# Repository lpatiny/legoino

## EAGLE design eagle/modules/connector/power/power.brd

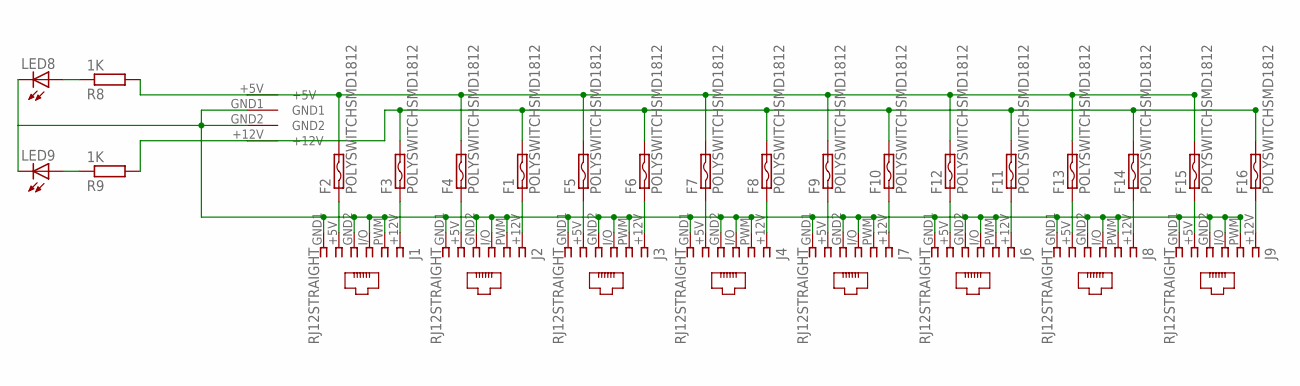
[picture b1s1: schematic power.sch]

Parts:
F1, F2, F3, F4, F5, F6, F7, F8, F9, F10, F11, F12, F13, F14, F15, F16: POLYSWITCHSMD1812; C1812
J1, J2, J3, J4, J6, J7, J8, J9: RJ12STRAIGHT; RJ12-STRAIGHT
LED8, LED9: LED3MM
R8, R9: 1K; M1206
U$1: KPJX-4S-S

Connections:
GND: J1.GND1 (6), J1.GND2 (4), J1.I/O (3), J1.PWM (2), J2.GND1 (6), J2.GND2 (4), J2.I/O (3), J2.PWM (2), J3.GND1 (6), J3.GND2 (4), J3.I/O (3), J3.PWM (2), J4.GND1 (6), J4.GND2 (4), J4.I/O (3), J4.PWM (2), J6.GND1 (6), J6.GND2 (4), J6.I/O (3), J6.PWM (2), J7.GND1 (6), J7.GND2 (4), J7.I/O (3), J7.PWM (2), J8.GND1 (6), J8.GND2 (4), J8.I/O (3), J8.PWM (2), J9.GND1 (6), J9.GND2 (4), J9.I/O (3), J9.PWM (2), LED8.K (C), LED9.K (C), U$1.GND1, U$1.GND2
unnamed: F2.1, J1.+5V (5)
unnamed: F3.1, J1.+12V (1)
unnamed: F4.1, J2.+5V (5)
unnamed: F1.1, J2.+12V (1)
unnamed: F5.1, J3.+5V (5)
unnamed: F6.1, J3.+12V (1)
unnamed: F7.1, J4.+5V (5)
unnamed: F9.1, J7.+5V (5)
unnamed: F8.1, J4.+12V (1)
unnamed: F10.1, J7.+12V (1)
unnamed: F11.1, J6.+12V (1)
unnamed: F12.1, J6.+5V (5)
unnamed: F13.1, J8.+5V (5)
unnamed: F14.1, J8.+12V (1)
unnamed: F15.1, J9.+5V (5)
unnamed: F16.1, J9.+12V (1)
unnamed: F2.2, F4.2, F5.2, F7.2, F9.2, F12.2, F13.2, F15.2, R8.2, U$1.+5V
unnamed: F1.2, F3.2, F6.2, F8.2, F10.2, F11.2, F14.2, F16.2, R9.2, U$1.+12V
unnamed: LED9.A, R9.1
unnamed: LED8.A, R8.1

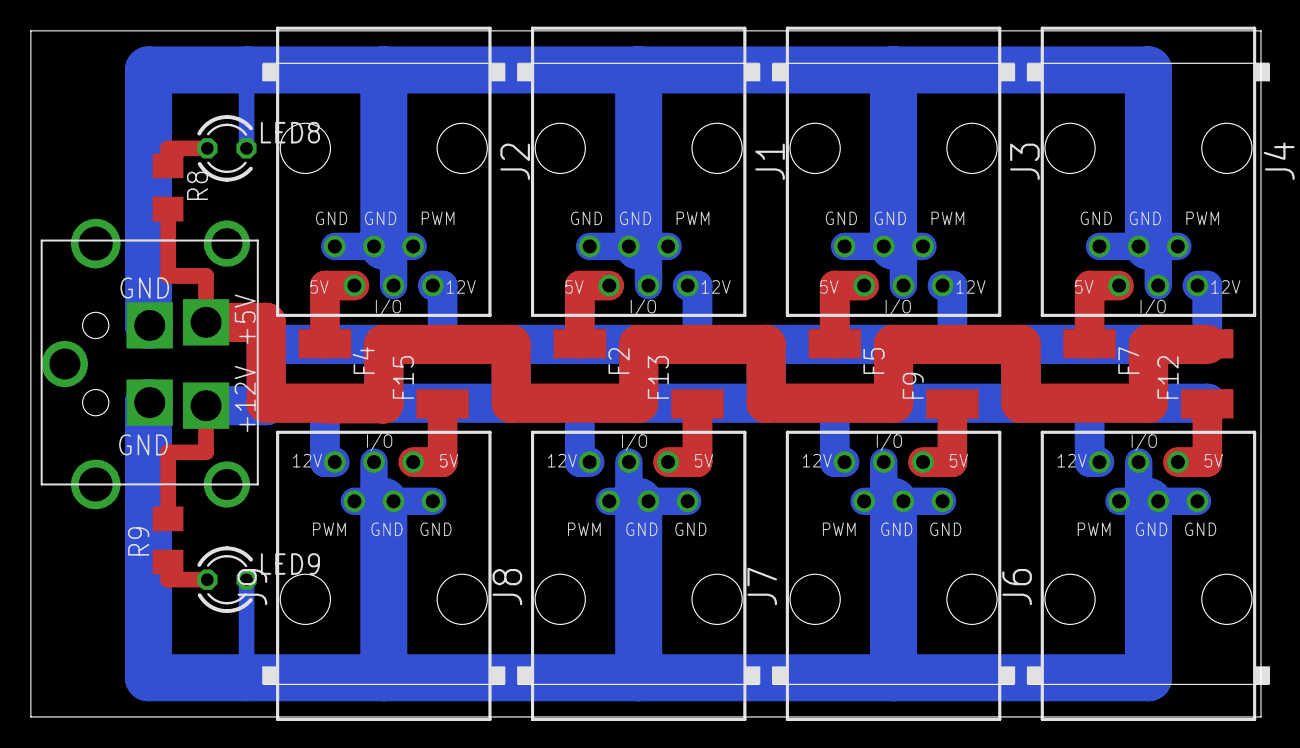
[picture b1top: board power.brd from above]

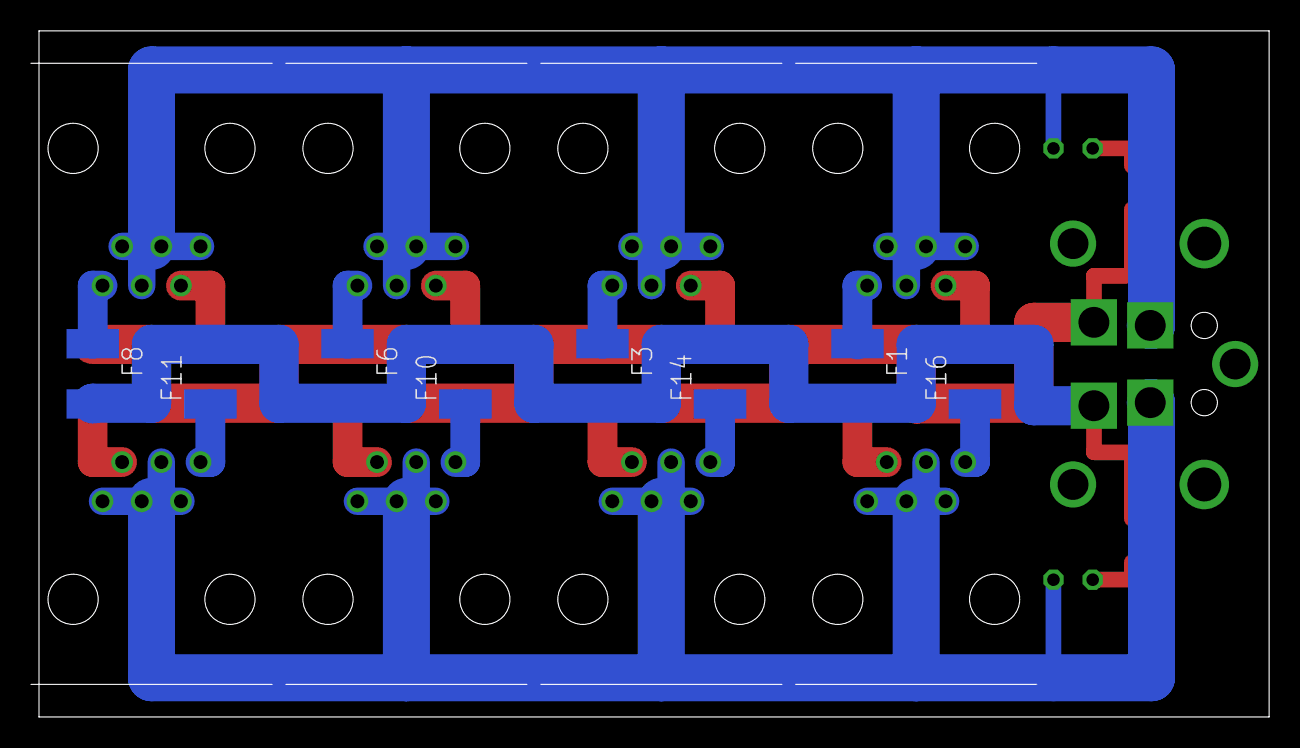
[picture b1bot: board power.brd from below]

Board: 2 copper layers, 80.2 x 44.4 mm, 29 parts (8 on the bottom side), 21 nets.

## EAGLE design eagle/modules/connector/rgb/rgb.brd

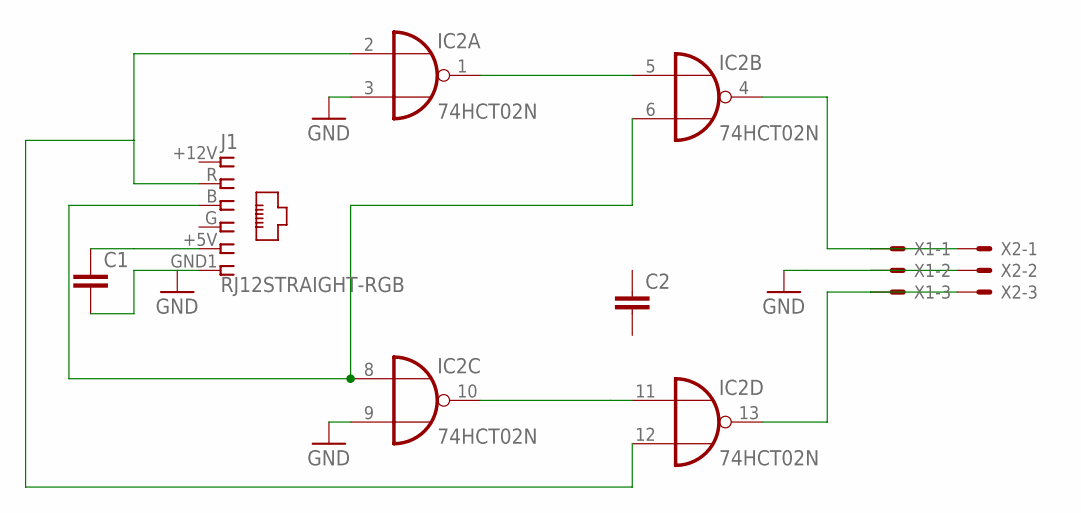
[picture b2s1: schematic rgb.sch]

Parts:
C1, C2: C-EU025-025X050; C025-025X050
IC2: 74HCT02N; DIL14
J1: RJ12STRAIGHT-RGB; RJ12-STRAIGHT-RGB
X1, X2: KK-156-3

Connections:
1: J1.+12V (1)
4: J1.G (4)
GND: C1.2, IC2.3 (I1), IC2.7 (GND), IC2.9 (I1), J1.GND1 (6), X1.2, X2.2
unnamed: IC2.2 (I0), IC2.12 (I1), J1.R (2)
unnamed: IC2.6 (I1), IC2.8 (I0), J1.B (3)
unnamed: IC2.1 (O), IC2.5 (I0)
unnamed: IC2.10 (O), IC2.11 (I0)
unnamed: IC2.4 (O), X1.1, X2.1
unnamed: IC2.13 (O), X1.3, X2.3
VCC: C1.1, IC2.14 (VCC), J1.+5V (5)

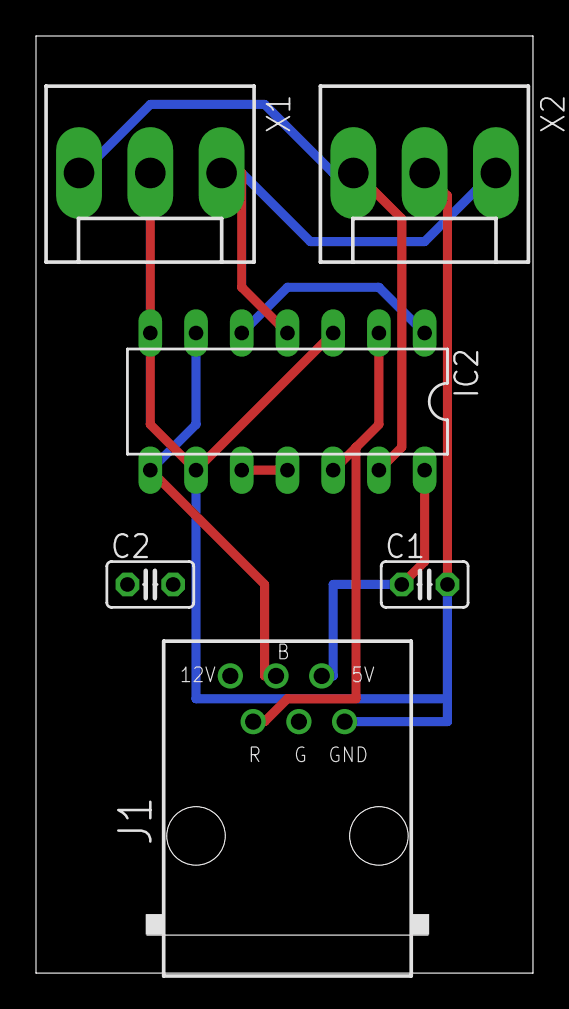
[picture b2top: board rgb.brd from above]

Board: 2 copper layers, 27.6 x 52.0 mm, 6 parts (0 on the bottom side), 8 nets.

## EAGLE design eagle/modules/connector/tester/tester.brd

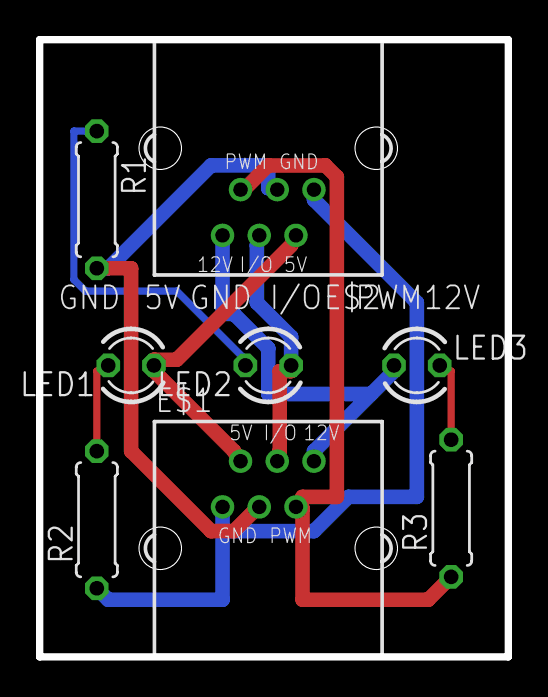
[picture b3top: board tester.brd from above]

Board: 2 copper layers, 26.0 x 34.3 mm, 8 parts (0 on the bottom side), 9 nets.

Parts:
E$1, E$2: YH-55-10
LED1, LED2, LED3: LED3MM
R1, R2, R3: 1K; 0207/7

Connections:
S$1: E$1.6, E$2.6, LED3.A
S$2: E$1.5, E$2.5, R3.1
S$3: E$1.4, E$2.4, LED2.A
S$4: E$1.3, E$2.3, R1.2
S$5: E$1.2, E$2.2, LED1.A
S$6: E$1.1, E$2.1, R2.1
S$7: LED1.K, R2.2
S$8: LED2.K, R1.1
S$9: LED3.K, R3.2

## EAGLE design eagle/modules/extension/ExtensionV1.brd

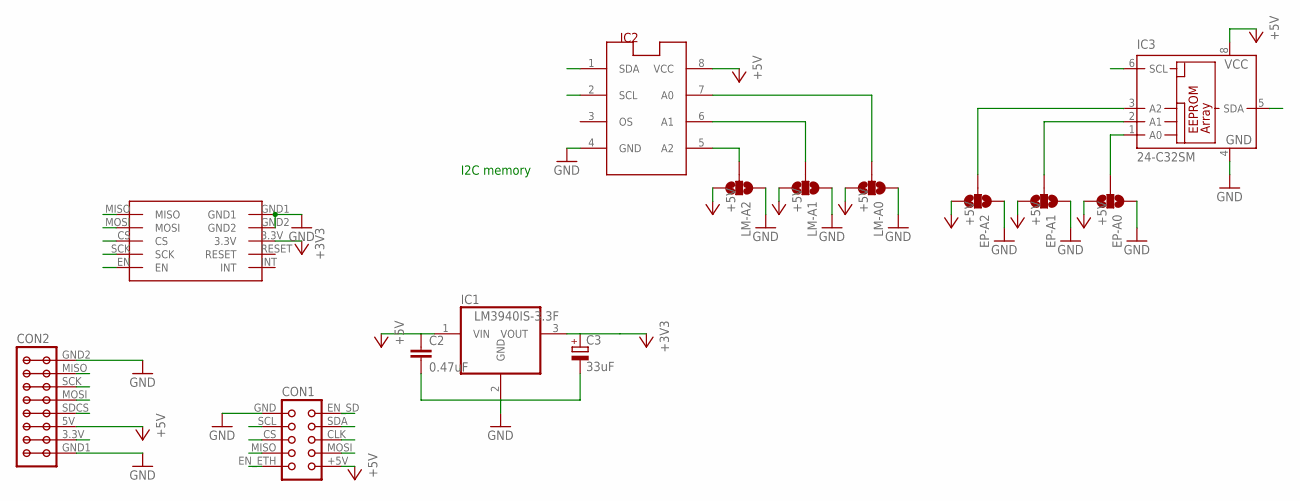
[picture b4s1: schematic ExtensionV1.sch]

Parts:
C2: 0.47uF; C1206
C3: 33uF; E3,5-8
CON1: CON10EXT
CON2: SD-CARD-EXTENSION; SD-CARD
EP-A0, EP-A1, EP-A2: SOLDERJUMPER_2WAY; 1206-SWITCH
IC1: LM3940IS-3.3F; DD-3
IC2: LM75_ICN; SO8_LM75
IC3: 24-C32SM; SO-08M
LM-A0, LM-A1, LM-A2: SOLDERJUMPER_2WAY; 1206-SWITCH
U$1: W5100

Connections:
+3V3: C3.+, IC1.3 (VOUT), U$1.3.3V
+5V: C2.1, CON1.+5V (1), CON2.5V, EP-A0.3, EP-A1.3, EP-A2.3, IC1.1 (VIN), IC2.8 (VCC), IC3.8 (VCC), LM-A0.3, LM-A1.3, LM-A2.3
CLK: CON1.CLK (5), CON2.SCK, U$1.SCK
CS: U$1.CS
EN_ETH: CON1.EN_ETH (2), U$1.EN
EN_SD: CON1.EN_SD (9), CON2.SDCS
GND: C2.2, C3.-, CON1.GND (10), CON2.GND1, CON2.GND2, EP-A0.1, EP-A1.1, EP-A2.1, IC1.2 (GND), IC2.4 (GND), IC3.4 (GND), LM-A0.1, LM-A1.1, LM-A2.1, U$1.GND1, U$1.GND2
MISO: CON2.MISO, U$1.MISO
MOSI: CON1.MOSI (3), CON2.MOSI, U$1.MOSI
MSIO: CON1.MISO (4)
unnamed: IC2.7 (A0), LM-A0.2
unnamed: IC2.6 (A1), LM-A1.2
unnamed: IC2.5 (A2), LM-A2.2
unnamed: EP-A0.2, IC3.1 (A0)
unnamed: EP-A1.2, IC3.2 (A1)
unnamed: EP-A2.2, IC3.3 (A2)
SCL: CON1.SCL (8), IC2.2 (SCL), IC3.6 (SCL)
SDA: CON1.SDA (7), IC2.1 (SDA), IC3.5 (SDA)

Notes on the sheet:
I2C memory

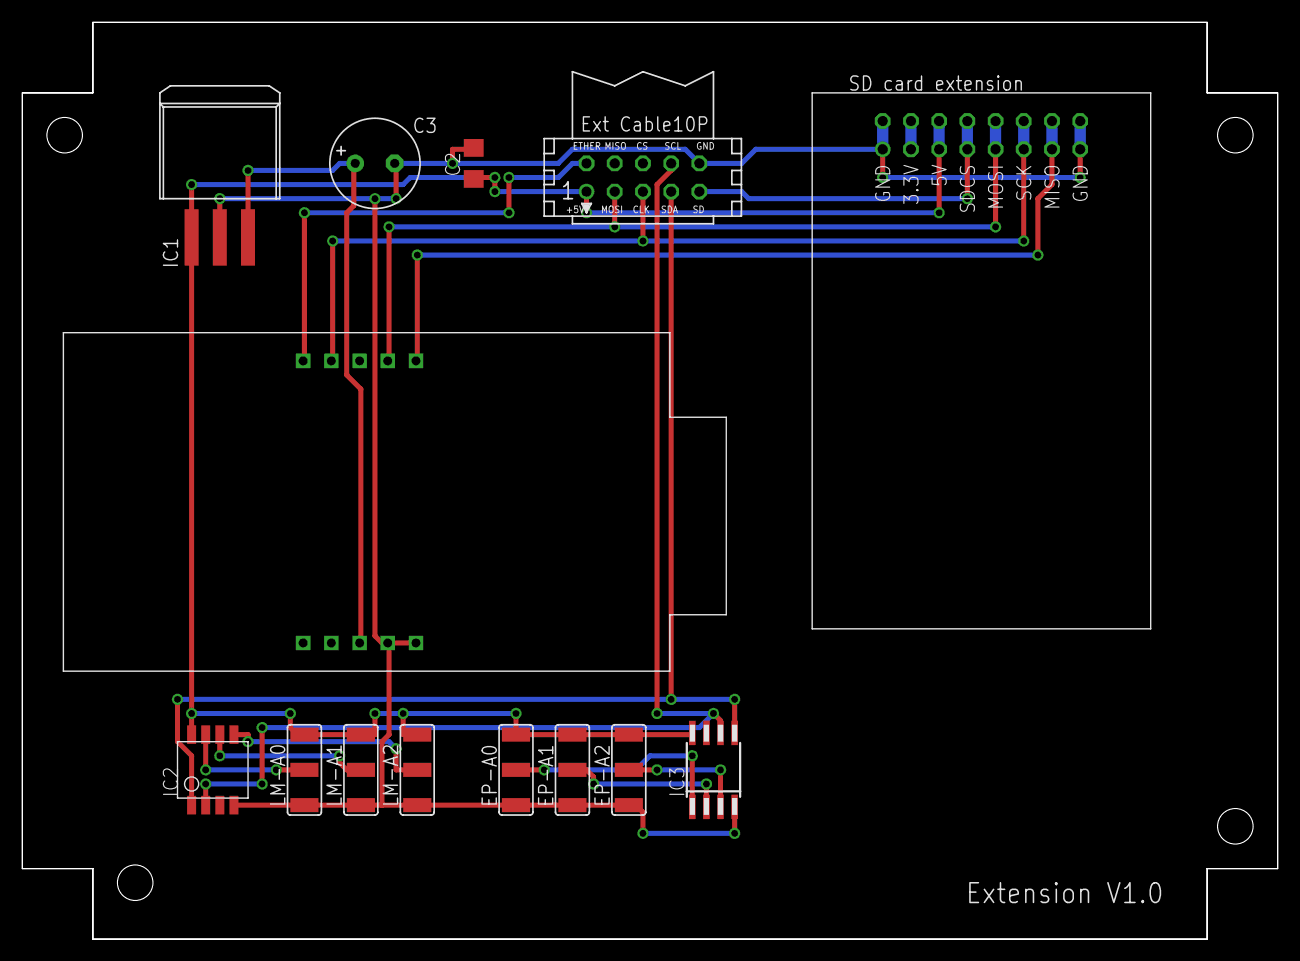
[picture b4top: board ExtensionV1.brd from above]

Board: 2 copper layers, 113.0 x 82.5 mm, 14 parts (0 on the bottom side), 16 nets.
